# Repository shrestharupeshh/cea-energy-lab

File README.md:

# PLANTPULSE LAB

Open experimental platform for multimodal plant phenotyping and physics-informed digital twins in
controlled-environment agriculture. Primary crop: lettuce (*Lactuca sativa*).

**Status (read this first).** This repository contains a complete *design*, a complete *software
stack tested against simulated hardware*, and a complete *experimental plan*. No hardware has been
built, no plant has been grown, and there are **no experimental results** here. Everything
numerical is either a design calculation, a model prediction, or simulated data, and is labelled
as such. See `docs/phases/PHASE_LOG.md` for what is done, what is open, and what needs physical work.

## Research theme

*Multimodal plant phenotyping and physics-informed digital twins for early stress detection and
resource-efficient controlled-environment agriculture.* Five research questions with
pre-specified hypotheses (`docs/research/hypotheses.md`), tested in separate studies
(`experiments/protocols/`), analysed by a plan written before any data exist
(`experiments/protocols/statistical_analysis_plan.md`).

## The instrument in one paragraph

Four independent growth pods (experimental unit = pod-run), six lettuce plants each in a
deep-water-culture tub; six dimmable Bridgelux LED strips above an acrylic window; ventilation
cooling, PTC heating, ultrasonic humidification; SHT45 / SCD30 / spectral PAR monitor / isolated
pH and EC / load-cell water accounting / per-rail power metering; a single-axis camera gantry
(Raspberry Pi HQ camera) parking outside the canopy; an ESP32-S3 node per pod running a
fail-safe controller; a Raspberry Pi 5 running acquisition, QC, vision, models and the dashboard.
Estimated cost about USD 1,650 per pod and USD 9,200 for the facility with shared reference
instruments (unverified prices).

## Repository map

| Path | Content |
|------|---------|
| `docs/research/` | literature review + matrix, research gap, hypotheses |
| `docs/requirements/`, `docs/architecture/` | requirements, trade studies, environmental control, electronics, data and software architecture |
| `docs/validation/` | validation plan (47 acceptance criteria), calibration procedures, uncertainty budget |
| `docs/manufacturing/` | BOM with sourcing, cost estimate, build guide |
| `docs/phases/PHASE_LOG.md` | per-phase deliverables, tests, open problems, assumptions, physical-work items |
| `hardware/design_parameters.yaml` | single source of truth for dimensions and component data |
| `hardware/mechanical/` | parametric CAD (CadQuery), STEP/STL/3MF/DXF, drawings, calculation report |
| `hardware/electrical/pcb/` | node carrier board: netlist source, KiCad schematic + PCB, Gerbers, DRC |
| `firmware/` | ESP32-S3 node firmware, serial protocol, host-side unit tests |
| `software/plantpulse/` | Python package (acquisition, data, vision, ML, twin, optimisation, stats, dashboard, simulation) |
| `experiments/` | protocols, analysis plans, data roots (raw / processed, git-ignored) |
| `simulation/` | virtual-study driver and reports (simulated data only) |
| `publications/` | strategy, outlines for three papers, figure scripts |
| `tests/` | 78 tests |

## Quick start (no hardware needed)

```bash
python -m venv .venv && . .venv/bin/activate
pip install -e ".[dashboard,dev]"
pytest                                            # ~2 min
python simulation/run_virtual_study.py --quick    # simulated Study A through the full pipeline
PLANTPULSE_DATA=simulation/output/lab_quick streamlit run software/plantpulse/dashboard/app.py
```

Regenerate engineering outputs: see `docs/architecture/software_architecture.md`.
CAD needs `pip install cadquery`; PCB scripts need KiCad 7 (`pcbnew` Python module, `kicad-cli`).

## Honest limits

- Pods cool by ventilation: the room must be ≤ 20 °C and pods cannot run below room temperature
  or dehumidify below room dew point. CO₂ is monitored, not enriched.
- n = 4 units per run. Replication comes from repeated runs; a full programme is about 13 crop
  cycles (over a year).
- A single top-view camera at 500 mm: strong perspective magnification with plant height;
  per-plant area becomes unreliable once canopies touch.
- The vision pipeline has only been run on procedurally generated images.
- The digital twin is uncalibrated; its recommendations are hypotheses and are blocked from
  driving hardware until validation tests pass and an experiment opts in.
- Firmware application layer not yet compiled for the target; PCB not fabricated; CNN code
  unexecuted (PyTorch unavailable in the build environment).
- Literature review is a scoping review; many citations still need verification.

## Licences

Software: MIT. Hardware (CAD, PCB): CERN-OHL-P-2.0. Documentation and data: CC BY 4.0.
See `LICENSE`.

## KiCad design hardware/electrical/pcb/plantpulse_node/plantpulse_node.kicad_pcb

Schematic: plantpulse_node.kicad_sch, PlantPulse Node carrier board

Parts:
C1: 100u/50V; CP_Radial_D8.0mm_P3.50mm
C2: 470u/35V; CP_Radial_D10.0mm_P5.00mm
C3, C4: 22u/25V; CP_Radial_D8.0mm_P3.50mm
C5: 100u/25V; CP_Radial_D8.0mm_P3.50mm
C6, C7, C9: 100n; C_Disc_D5.0mm_W2.5mm_P5.00mm
C8: 100u/35V; CP_Radial_D8.0mm_P3.50mm
D1, D4, D5: 1N5819; D_DO-41_SOD81_P10.16mm_Horizontal; MPN 1N5819
D2, D3: P6KE27A; D_DO-15_P12.70mm_Horizontal; MPN P6KE27A
F1: 1A T; Fuseholder_Cylinder-5x20mm_Schurter_0031_8201_Horizontal_Op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; MPN 0031.8201
J1: PWR_IN; TerminalBlock_Phoenix_MKDS-1,5-4-5.08_1x04_P5.08mm_Horizont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; MPN 1715747
J2: HEATER; TerminalBlock_Phoenix_MKDS-1,5-2-5.08_1x02_P5.08mm_Horizont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; MPN 1715721
J3: PUMP; JST_XH_B2B-XH-A_1x02_P2.50mm_Vertical; MPN B2B-XH-A
J4: PERI; JST_XH_B2B-XH-A_1x02_P2.50mm_Vertical; MPN B2B-XH-A
J5: HUMID; JST_XH_B2B-XH-A_1x02_P2.50mm_Vertical; MPN B2B-XH-A
J6: IMG_LED; JST_XH_B2B-XH-A_1x02_P2.50mm_Vertical; MPN B2B-XH-A
J7: LED_DIM; JST_XH_B3B-XH-A_1x03_P2.50mm_Vertical; MPN B3B-XH-A
J10: FAN1; FanPinHeader_1x04_P2.54mm_Vertical; MPN 47053-1000
J11: FAN2; FanPinHeader_1x04_P2.54mm_Vertical; MPN 47053-1000
J12: FAN3; FanPinHeader_1x04_P2.54mm_Vertical; MPN 47053-1000
J20: ESP32-S3 L; PinSocket_1x22_P2.54mm_Vertical; MPN ESP32-S3-DevKitC-1-N8R2
J21: ESP32-S3 R (22.86); PinSocket_1x22_P2.54mm_Vertical
J22: ESP32-S3 R (25.40); PinSocket_1x22_P2.54mm_Vertical
J30: TMC2209 A; PinSocket_1x08_P2.54mm_Vertical; MPN TMC2209 SilentStepStick
J31: TMC2209 B; PinSocket_1x08_P2.54mm_Vertical
J32: MOTOR; JST_XH_B4B-XH-A_1x04_P2.50mm_Vertical; MPN B4B-XH-A
J33: ENDSTOP; JST_XH_B3B-XH-A_1x03_P2.50mm_Vertical; MPN B3B-XH-A
J40: SHT45; JST_XH_B4B-XH-A_1x04_P2.50mm_Vertical; MPN B4B-XH-A
J41: SCD30; JST_XH_B4B-XH-A_1x04_P2.50mm_Vertical; MPN B4B-XH-A
J42: AS7341; JST_XH_B4B-XH-A_1x04_P2.50mm_Vertical; MPN B4B-XH-A
J43: NAU7802; JST_XH_B4B-XH-A_1x04_P2.50mm_Vertical; MPN B4B-XH-A
J44: EZO_PH; JST_XH_B4B-XH-A_1x04_P2.50mm_Vertical; MPN B4B-XH-A
J45: EZO_EC; JST_XH_B4B-XH-A_1x04_P2.50mm_Vertical; MPN B4B-XH-A
J46: INA228_A; JST_XH_B4B-XH-A_1x04_P2.50mm_Vertical; MPN B4B-XH-A
J47: INA228_B; JST_XH_B4B-XH-A_1x04_P2.50mm_Vertical; MPN B4B-XH-A
J50: DS18B20_A; JST_XH_B3B-XH-A_1x03_P2.50mm_Vertical; MPN B3B-XH-A
J51: DS18B20_B; JST_XH_B3B-XH-A_1x03_P2.50mm_Vertical; MPN B3B-XH-A
J52: FLOW; JST_XH_B3B-XH-A_1x03_P2.50mm_Vertical; MPN B3B-XH-A
J53: CAMERA; JST_XH_B4B-XH-A_1x04_P2.50mm_Vertical; MPN B4B-XH-A
J60: FLOAT_LO; JST_XH_B2B-XH-A_1x02_P2.50mm_Vertical; MPN B2B-XH-A
J61: FLOAT_HI; JST_XH_B2B-XH-A_1x02_P2.50mm_Vertical; MPN B2B-XH-A
J62: LEAK; JST_XH_B2B-XH-A_1x02_P2.50mm_Vertical; MPN B2B-XH-A
J63: DOOR; JST_XH_B2B-XH-A_1x02_P2.50mm_Vertical; MPN B2B-XH-A
J64: EXP; PinHeader_1x06_P2.54mm_Vertical
Q1, Q2, Q3, Q4, Q5: IRLB8721; TO-220-3_Vertical; MPN IRLB8721PBF
Q10, Q11, Q12: 2N7000; TO-92_Inline_Wide; MPN 2N7000
R1: 100k; R_Axial_DIN0207_L6.3mm_D2.5mm_P10.16mm_Horizontal
R2: 12k; R_Axial_DIN0207_L6.3mm_D2.5mm_P10.16mm_Horizontal
R3, R4: 2k2; R_Axial_DIN0207_L6.3mm_D2.5mm_P10.16mm_Horizontal
R5: 4k7; R_Axial_DIN0207_L6.3mm_D2.5mm_P10.16mm_Horizontal
R6, R7, R11, R13, R15, R17, R19, R30, R31, R32, R33, R40, R41, R42, R43: 10k; R_Axial_DIN0207_L6.3mm_D2.5mm_P10.16mm_Horizontal
R10, R12, R14, R16, R18: 100R; R_Axial_DIN0207_L6.3mm_D2.5mm_P10.16mm_Horizontal
R34: 20k; R_Axial_DIN0207_L6.3mm_D2.5mm_P10.16mm_Horizontal
U1, U2: TSR 1-2450; Converter_DCDC_TRACO_TSR-1_THT; MPN TSR 1-2450
U3: TSR 2-24120; Converter_DCDC_TRACO_TSR-1_THT; MPN TSR 2-24120
U4: 74HCT541; DIP-20_W7.62mm; MPN SN74HCT541N
U5: MCP23017; DIP-28_W7.62mm; MPN MCP23017-E/SP

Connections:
+3V3: C6.1, C9.1, J20.1, J20.2, J30.2, J30.3, J31.7, J33.1, J40.1, J41.1, J42.1, J43.1, J44.1, J45.1, J46.1, J47.1, J50.1, J51.1, J64.1, R3.1, R4.1, R5.1, R30.1, R31.1, R32.1, R40.1, R41.1, R42.1, R43.1, U5.9 (VDD), U5.18 (~RESET)
+5V: C3.1, C7.1, J5.1, J20.21, J52.1, R6.1, U1.3 (Vout), U4.20 (VCC)
+5V_CAM: C4.1, J53.1, U2.3 (Vout)
+12V: C5.1, D4.1 (K), D5.1 (K), J3.1, J4.1, J6.1, J10.2, J11.2, J12.2, U3.3 (Vout)
+24V_ACT: C2.1, C8.1, D3.1 (A1), J1.3, J2.1, J31.1, R1.1, U3.1 (Vin)
+24V_L: C1.1, D1.1 (K), D2.1 (A1), U1.1 (Vin), U2.1 (Vin)
+24V_LOGIC_F: D1.2 (A), F1.2
+24V_LOGIC_IN: F1.1, J1.2
CAM_BUSY: J20.8, J53.4
CAM_TRIG: J20.7, J53.3
DIR: J21.7, J22.7, J30.8
DOOR: J63.1, R43.2, U5.24 (GPA3)
ENDSTOP: J21.17, J22.17, J33.3, R32.2
ESTOP_OK: R1.2, R2.1, U5.25 (GPA4)
EXP_INT: J21.5, J22.5, U5.20 (INTA)
FAN1_OD: J10.4, Q10.3 (D)
FAN1_PWM: J20.16, Q10.2 (G)
FAN2_OD: J11.4, Q11.3 (D)
FAN2_PWM: J20.17, Q11.2 (G)
FAN3_OD: J12.4, Q12.3 (D)
FAN3_PWM: J20.18, Q12.2 (G)
FLOAT_HI: J61.1, R41.2, U5.22 (GPA1)
FLOAT_LO: J60.1, R40.2, U5.21 (GPA0)
FLOW: J21.4, J22.4, R33.2, R34.1
FLOW_5V: J52.3, R33.1
GND: C1.2, C2.2, C3.2, C4.2, C5.2, C6.2, C7.2, C8.2, C9.2, D2.2 (A2), D3.2 (A2), J1.1, J1.4, J7.2, J7.3, J10.1, J11.1, J12.1, J20.22, J21.1, J21.21, J21.22, J22.1, J22.21, J22.22, J30.6, J31.2, J31.8, J33.2, J40.2, J41.2, J42.2, J43.2, J44.2, J45.2, J46.2, J47.2, J50.2, J51.2, J52.2, J53.2, J60.2, J61.2, J62.2, J63.2, J64.2, Q1.3 (S), Q2.3 (S), Q3.3 (S), Q4.3 (S), Q5.3 (S), Q10.1 (S), Q11.1 (S), Q12.1 (S), R2.2, R7.2, R11.2, R13.2, R15.2, R17.2, R19.2, R34.2, U1.2 (GND), U2.2 (GND), U3.2 (GND), U4.8 (A6), U4.9 (A7), U4.10 (GND), U5.10 (VSS), U5.15 (A0), U5.16 (A1), U5.17 (A2)
GPB0: J64.3, U5.1 (GPB0)
GPB1: J64.4, U5.2 (GPB1)
GPB2: J64.5, U5.3 (GPB2)
GPB3: J64.6, U5.4 (GPB3)
HEATER: J20.9, U4.2 (A0)
HEATER_SW: J2.2, Q1.2 (D)
HEAT_G: Q1.1 (G), R10.2, R11.1
HEAT_G5: R10.1, U4.18 (Y0)
HUMID: J21.18, J22.18, U4.5 (A3)
HUM_G: Q4.1 (G), R16.2, R17.1
HUM_G5: R16.1, U4.15 (Y3)
HUM_SW: J5.2, Q4.2 (D)
IMG_G: Q5.1 (G), R18.2, R19.1
IMG_G5: R18.1, U4.14 (Y4)
IMG_LED: J20.6, U4.6 (A4)
IMG_SW: J6.2, Q5.2 (D)
LEAK: J62.1, R42.2, U5.23 (GPA2)
LED_PWM: J20.5, U4.7 (A5)
LED_PWM_5V: J7.1, R7.1, U4.13 (Y5)
M_A1: J31.5, J32.3
M_A2: J31.6, J32.4
M_B1: J31.4, J32.2
M_B2: J31.3, J32.1
OUT_EN_N: J21.9, J22.9, R6.2, U4.1 (G1), U4.19 (G2)
OW: J20.4, J50.3, J51.3, R5.2
PERI: J20.11, U4.4 (A2)
PERI_G: Q3.1 (G), R14.2, R15.1
PERI_G5: R14.1, U4.16 (Y2)
PERI_SW: D5.2 (A), J4.2, Q3.2 (D)
PUMP: J20.10, U4.3 (A1)
PUMP_G: Q2.1 (G), R12.2, R13.1
PUMP_G5: R12.1, U4.17 (Y1)
PUMP_SW: D4.2 (A), J3.2, Q2.2 (D)
SCL: J20.15, J40.4, J41.4, J42.4, J43.4, J44.4, J45.4, J46.4, J47.4, R4.2, U5.12 (SCK)
SDA: J20.12, J40.3, J41.3, J42.3, J43.3, J44.3, J45.3, J46.3, J47.3, R3.2, U5.13 (SDA)
STEP: J21.8, J22.8, J30.7
STEP_EN_N: J21.6, J22.6, J30.1
TACH1: J10.3, J20.19, R30.2
TACH2: J11.3, J20.20, R31.2

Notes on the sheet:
POWER ENTRY, PROTECTION, REGULATION
MCU SOCKET (ESP32-S3-DevKitC-1) AND BUS PULL-UPS
FAIL-SAFE OUTPUT BUFFER AND LOW-SIDE SWITCHES
PWM FANS
GANTRY STEPPER
SENSOR CONNECTORS
I/O EXPANDER AND SWITCH INPUTS

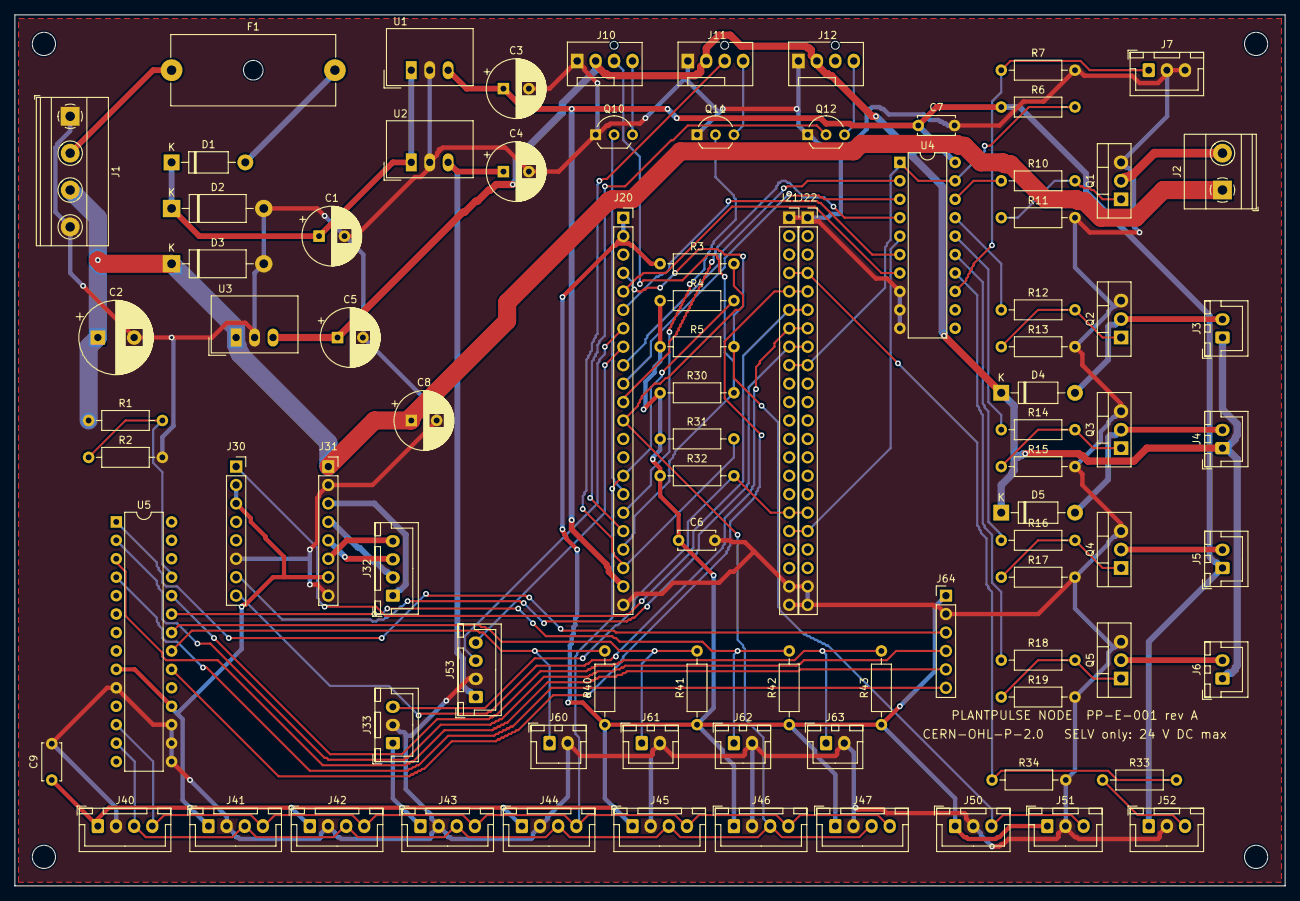
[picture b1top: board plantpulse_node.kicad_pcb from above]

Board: 2 copper layers, 175.0 x 120.0 mm, 92 parts (0 on the bottom side), 65 nets.

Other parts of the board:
H344, H345, H346, H347: MountingHole_3.2mm_M3

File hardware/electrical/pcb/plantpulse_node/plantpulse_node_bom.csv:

qty,references,value,footprint,mpn,description
1,C1,100u/50V,CP_Radial_D8.0mm_P3.50mm,,"Bulk, logic feed"
1,C2,470u/35V,CP_Radial_D10.0mm_P5.00mm,,"Bulk, actuator feed"
2,C3 C4,22u/25V,CP_Radial_D8.0mm_P3.50mm,,
1,C5,100u/25V,CP_Radial_D8.0mm_P3.50mm,,
3,C6 C7 C9,100n,C_Disc_D5.0mm_W2.5mm_P5.00mm,,
1,C8,100u/35V,CP_Radial_D8.0mm_P3.50mm,,Stepper VMOT bulk
3,D1 D4 D5,1N5819,D_DO-41_SOD81_P10.16mm_Horizontal,1N5819,"Reverse-polarity Schottky, logic feed"
2,D2 D3,P6KE27A,D_DO-15_P12.70mm_Horizontal,P6KE27A,"TVS, logic feed"
1,F1,1A T,Fuseholder_Cylinder-5x20mm_Schurter_0031_8201_Horizontal_Open,0031.8201,5x20 fuse holder + 1 A slow fuse (logic feed)
1,J1,PWR_IN,"TerminalBlock_Phoenix_MKDS-1,5-4-5.08_1x04_P5.08mm_Horizontal",1715747,Power input: GND / 24V logic / 24V actuators / GND
1,J10,FAN1,FanPinHeader_1x04_P2.54mm_Vertical,47053-1000,4-pin PWM fan 1
1,J11,FAN2,FanPinHeader_1x04_P2.54mm_Vertical,47053-1000,4-pin PWM fan 2
1,J12,FAN3,FanPinHeader_1x04_P2.54mm_Vertical,47053-1000,4-pin PWM fan 3
1,J2,HEATER,"TerminalBlock_Phoenix_MKDS-1,5-2-5.08_1x02_P5.08mm_Horizontal",1715721,PTC heater (via external 45 C thermostat)
1,J20,ESP32-S3 L,PinSocket_1x22_P2.54mm_Vertical,ESP32-S3-DevKitC-1-N8R2,DevKitC-1 left header socket
1,J21,ESP32-S3 R (22.86),PinSocket_1x22_P2.54mm_Vertical,,"DevKitC-1 right header socket, 22.86 mm row spacing"
1,J22,ESP32-S3 R (25.40),PinSocket_1x22_P2.54mm_Vertical,,"Alternative right socket position, 25.4 mm row spacing (fit one)"
1,J3,PUMP,JST_XH_B2B-XH-A_1x02_P2.50mm_Vertical,B2B-XH-A,Circulation pump
1,J30,TMC2209 A,PinSocket_1x08_P2.54mm_Vertical,TMC2209 SilentStepStick,"Stepper driver socket, logic side (MS1 = MS2 = high: 1/16)"
1,J31,TMC2209 B,PinSocket_1x08_P2.54mm_Vertical,,"Stepper driver socket, motor side"
1,J32,MOTOR,JST_XH_B4B-XH-A_1x04_P2.50mm_Vertical,B4B-XH-A,NEMA17 gantry motor
1,J33,ENDSTOP,JST_XH_B3B-XH-A_1x03_P2.50mm_Vertical,B3B-XH-A,Gantry home switch
1,J4,PERI,JST_XH_B2B-XH-A_1x02_P2.50mm_Vertical,B2B-XH-A,Peristaltic top-up pump
1,J40,SHT45,JST_XH_B4B-XH-A_1x04_P2.50mm_Vertical,B4B-XH-A,I2C: SHT45
1,J41,SCD30,JST_XH_B4B-XH-A_1x04_P2.50mm_Vertical,B4B-XH-A,I2C: SCD30
1,J42,AS7341,JST_XH_B4B-XH-A_1x04_P2.50mm_Vertical,B4B-XH-A,I2C: AS7341
1,J43,NAU7802,JST_XH_B4B-XH-A_1x04_P2.50mm_Vertical,B4B-XH-A,I2C: NAU7802
1,J44,EZO_PH,JST_XH_B4B-XH-A_1x04_P2.50mm_Vertical,B4B-XH-A,I2C: EZO_PH
1,J45,EZO_EC,JST_XH_B4B-XH-A_1x04_P2.50mm_Vertical,B4B-XH-A,I2C: EZO_EC
1,J46,INA228_A,JST_XH_B4B-XH-A_1x04_P2.50mm_Vertical,B4B-XH-A,I2C: INA228_A
1,J47,INA228_B,JST_XH_B4B-XH-A_1x04_P2.50mm_Vertical,B4B-XH-A,I2C: INA228_B
1,J5,HUMID,JST_XH_B2B-XH-A_1x02_P2.50mm_Vertical,B2B-XH-A,Ultrasonic humidifier module
1,J50,DS18B20_A,JST_XH_B3B-XH-A_1x03_P2.50mm_Vertical,B3B-XH-A,1-Wire: solution temperature
1,J51,DS18B20_B,JST_XH_B3B-XH-A_1x03_P2.50mm_Vertical,B3B-XH-A,1-Wire: heater outlet / spare
1,J52,FLOW,JST_XH_B3B-XH-A_1x03_P2.50mm_Vertical,B3B-XH-A,Hall flow meter
1,J53,CAMERA,JST_XH_B4B-XH-A_1x04_P2.50mm_Vertical,B4B-XH-A,"Camera node (Pi Zero 2 W): power, trigger, busy"
1,J6,IMG_LED,JST_XH_B2B-XH-A_1x02_P2.50mm_Vertical,B2B-XH-A,Imaging LED ring
1,J60,FLOAT_LO,JST_XH_B2B-XH-A_1x02_P2.50mm_Vertical,B2B-XH-A,Switch input: FLOAT_LO
1,J61,FLOAT_HI,JST_XH_B2B-XH-A_1x02_P2.50mm_Vertical,B2B-XH-A,Switch input: FLOAT_HI
1,J62,LEAK,JST_XH_B2B-XH-A_1x02_P2.50mm_Vertical,B2B-XH-A,Switch input: LEAK
1,J63,DOOR,JST_XH_B2B-XH-A_1x02_P2.50mm_Vertical,B2B-XH-A,Switch input: DOOR
1,J64,EXP,PinHeader_1x06_P2.54mm_Vertical,,Spare expander I/O
1,J7,LED_DIM,JST_XH_B3B-XH-A_1x03_P2.50mm_Vertical,B3B-XH-A,PWM to LED constant-current drivers
5,Q1 Q2 Q3 Q4 Q5,IRLB8721,TO-220-3_Vertical,IRLB8721PBF,Low-side switch: HEAT
3,Q10 Q11 Q12,2N7000,TO-92_Inline_Wide,2N7000,Open-drain fan PWM (inverting)
1,R1,100k,R_Axial_DIN0207_L6.3mm_D2.5mm_P10.16mm_Horizontal,,E-stop sense divider (24 V present)
5,R10 R12 R14 R16 R18,100R,R_Axial_DIN0207_L6.3mm_D2.5mm_P10.16mm_Horizontal,,Gate resistor
1,R2,12k,R_Axial_DIN0207_L6.3mm_D2.5mm_P10.16mm_Horizontal,,
2,R3 R4,2k2,R_Axial_DIN0207_L6.3mm_D2.5mm_P10.16mm_Horizontal,,I2C pull-up
1,R34,20k,R_Axial_DIN0207_L6.3mm_D2.5mm_P10.16mm_Horizontal,,
1,R5,4k7,R_Axial_DIN0207_L6.3mm_D2.5mm_P10.16mm_Horizontal,,1-Wire pull-up
15,R6 R11 R13 R15 R17 R19 R7 R30 R31 R32 R33 R40 R41 R42 R43,10k,R_Axial_DIN0207_L6.3mm_D2.5mm_P10.16mm_Horizontal,,Output-enable pull-up (outputs off by default)
2,U1 U2,TSR 1-2450,Converter_DCDC_TRACO_TSR-1_THT,TSR 1-2450,5 V 1 A switching regulator (logic)
1,U3,TSR 2-24120,Converter_DCDC_TRACO_TSR-1_THT,TSR 2-24120,"12 V 2 A switching regulator (fans, pumps, imaging LED)"
1,U4,74HCT541,DIP-20_W7.62mm,SN74HCT541N,3.3 V -> 5 V gate buffer; outputs hi-Z until OUT_EN_N is driven low
1,U5,MCP23017,DIP-28_W7.62mm,MCP23017-E/SP,I2C I/O expander (0x20): slow digital inputs

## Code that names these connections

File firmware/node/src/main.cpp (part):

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
// ---- pin map (see hardware/electrical/pcb/node_netlist.py)
namespace pin {
const int SDA = 8, SCL = 9, OW = 4, LED_PWM = 5, IMG_LED = 6, CAM_TRIG = 7, CAM_BUSY = 15;
const int HEATER = 16, PUMP = 17, PERI = 18, HUMID = 21;
const int FAN_PWM[3] = {10, 11, 12};        // exhaust, mixing, LED bay (inverted by 2N7000)
const int TACH[2] = {13, 14};
const int FLOW = 1, EXP_INT = 2, STEP_EN_N = 42, DIR = 41, STEP = 40, OUT_EN_N = 39, ENDSTOP = 47;
}  // namespace pin
namespace xp { const int FLOAT_LO = 0, FLOAT_HI = 1, LEAK = 2, DOOR = 3, ESTOP_OK = 4; }  // MCP23017 port A

// LEDC channels
enum { CH_LED = 0, CH_HEAT = 1, CH_FAN0 = 2, CH_FAN1 = 3, CH_FAN2 = 4 };
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  set_duty(CH_FAN0, o.fan, true);
  set_duty(CH_FAN1, o.mix, true);
  set_duty(CH_FAN2, o.led > 0.02f ? 0.3f + 0.7f * o.led : 0.0f, true);   // LED bay fan follows LED power
  digitalWrite(pin::PUMP, o.pump);
  digitalWrite(pin::PERI, o.topup);
  digitalWrite(pin::HUMID, o.humidifier);
  if (!o.gantry_enable) { stepper.stop(); }
}

void home_gantry() {
  digitalWrite(pin::STEP_EN_N, LOW);
  stepper.setMaxSpeed(1600); stepper.setAcceleration(4000);
  stepper.move(-60000);
  uint32_t t0 = millis();
  while (digitalRead(pin::ENDSTOP) == HIGH && millis() - t0 < 30000) { stepper.run(); esp_task_wdt_reset(); }
  stepper.setCurrentPosition(0);
  stepper.runToNewPosition(160);              // back off 2 mm, re-approach slowly for repeatability
  stepper.setMaxSpeed(160);
  stepper.move(-400);
  while (digitalRead(pin::ENDSTOP) == HIGH && stepper.distanceToGo() != 0) stepper.run();
  homed = digitalRead(pin::ENDSTOP) == LOW;
  stepper.setCurrentPosition(0);
  stepper.setMaxSpeed(4000);
  digitalWrite(pin::STEP_EN_N, HIGH);
}

void handle_line(const char* line) {
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  if (r.time_set) { epoch_at_sync = r.epoch; ms_at_sync = millis(); }
  if (r.move) {
    if (!homed) home_gantry();
    digitalWrite(pin::STEP_EN_N, LOW);
    stepper.moveTo(gantry.steps_for(r.station));
  }
  if (r.capture && img_state == ImgState::IDLE) { img_state = ImgState::LEDS_OFF; img_t0 = millis(); }
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  switch (img_state) {
    case ImgState::IDLE: break;
    case ImgState::LEDS_OFF:                  // grow LEDs off, imaging ring on, settle 500 ms
      img_blank = true; set_duty(CH_LED, 0); digitalWrite(pin::IMG_LED, HIGH);
      if (millis() - img_t0 > 500) { digitalWrite(pin::CAM_TRIG, HIGH); img_state = ImgState::WAIT_CAM; img_t0 = millis(); }
      break;
    case ImgState::WAIT_CAM:                  // camera node raises BUSY while exposing; 4 s timeout
      if ((millis() - img_t0 > 300 && digitalRead(pin::CAM_BUSY) == LOW) || millis() - img_t0 > 4000) {
        digitalWrite(pin::CAM_TRIG, LOW); digitalWrite(pin::IMG_LED, LOW); img_blank = false;
        Serial.printf("{\"t\":\"E\",\"ev\":\"capture_done\",\"ms\":%lu,\"pos\":%ld}\n", millis(), stepper.currentPosition());
        img_state = ImgState::IDLE;
      }
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
void setup() {
  // Outputs stay disabled (buffer hi-Z, gates pulled down) until setup has finished.
  pinMode(pin::OUT_EN_N, OUTPUT); digitalWrite(pin::OUT_EN_N, HIGH);
  for (int p : {pin::PUMP, pin::PERI, pin::HUMID, pin::IMG_LED, pin::CAM_TRIG, pin::STEP_EN_N}) { pinMode(p, OUTPUT); digitalWrite(p, LOW); }
  digitalWrite(pin::STEP_EN_N, HIGH);
  pinMode(pin::CAM_BUSY, INPUT_PULLDOWN); pinMode(pin::ENDSTOP, INPUT_PULLUP); pinMode(pin::FLOW, INPUT);
  for (int t : pin::TACH) pinMode(t, INPUT_PULLUP);
  ledcSetup(CH_LED, 1000, 10); ledcAttachPin(pin::LED_PWM, CH_LED);
  ledcSetup(CH_HEAT, 10, 10); ledcAttachPin(pin::HEATER, CH_HEAT);
  for (int i = 0; i < 3; ++i) { ledcSetup(CH_FAN0 + i, 25000, 10); ledcAttachPin(pin::FAN_PWM[i], CH_FAN0 + i); set_duty(CH_FAN0 + i, 0, true); }
  Serial.begin(115200);
  Wire.begin(pin::SDA, pin::SCL, 100000);
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  present.mcp = mcp.begin_I2C(0x20);
  if (present.mcp) for (int i = 0; i < 8; ++i) mcp.pinMode(i, INPUT);
  ds.begin(); ds.setWaitForConversion(false); ds.setResolution(12);
  attachInterrupt(pin::FLOW, isr_flow, RISING);
  attachInterrupt(pin::TACH[0], isr_tach0, FALLING);
  attachInterrupt(pin::TACH[1], isr_tach1, FALLING);
  esp_task_wdt_init(8, true); esp_task_wdt_add(NULL);
  Serial.printf("{\"t\":\"H\",\"pod\":%d,\"fw\":\"0.1.0\",\"sht\":%d,\"scd\":%d,\"as\":%d,\"nau\":%d,\"ina\":%d,\"mcp\":%d}\n",
                PP_POD_ID, present.sht, present.scd, present.as7341, present.nau, present.ina_led + present.ina_act, present.mcp);
  digitalWrite(pin::OUT_EN_N, LOW);           // enable the output buffer only now
}

void loop() {
  static char line[160]; static size_t n = 0; static uint32_t t_ctl = 0;
  esp_task_wdt_reset();
  stepper.run();
  if (stepper.distanceToGo() == 0 && img_state == ImgState::IDLE) digitalWrite(pin::STEP_EN_N, HIGH);
  while (Serial.available()) {
    char ch = Serial.read();
    if (ch == '\n') { line[n] = 0; if (n) handle_line(line); n = 0; }
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

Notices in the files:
hardware/electrical/pcb/plantpulse_node/plantpulse_node.kicad_pcb:
CERN-OHL-P-2.0 SELV only: 24 V DC max
